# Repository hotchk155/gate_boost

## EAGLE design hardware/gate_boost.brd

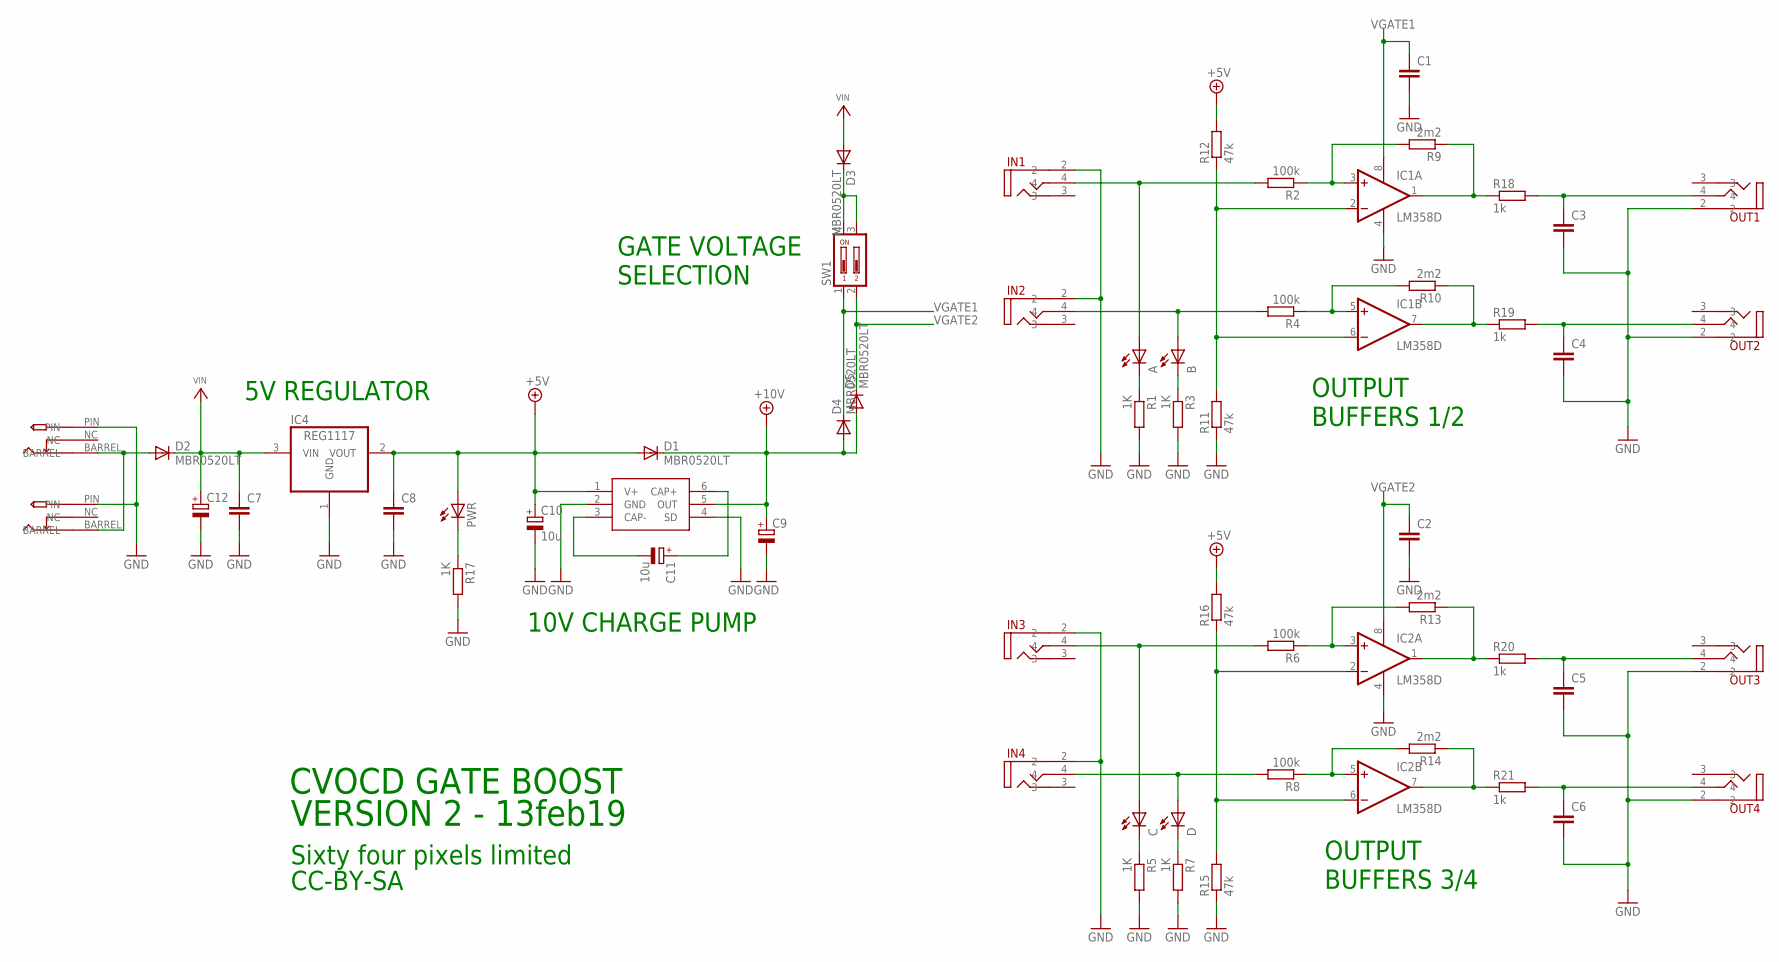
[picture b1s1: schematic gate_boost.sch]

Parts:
A: LED3MM
B: LED3MM
C: LED3MM
C1, C2, C3, C4, C5, C6, C7, C8: C-EUC0805; C0805
C9: CPOL-EUSMCA; SMC_A
C10, C11: 10u; SMC_A
C12: CPOL-EUE2-5; E2-5
D: LED3MM
D1, D2, D3, D4, D5: MBR0520LT; SOD123
IC1, IC2: LM358D; SO08
IC3: LM27675M5_CHARGEPUMP; SOT23-6
IC4: REG1117; SOT223
IN1, IN2, IN3, IN4: VERTICAL_3_5MM_SOCKET
OUT1, OUT2, OUT3, OUT4: VERTICAL_3_5MM_SOCKET
PWR: LED3MM
R1, R3, R5, R7, R17: 1K; R0805
R2, R4, R6, R8: 100k; R0805
R9, R10, R13, R14: 2m2; R0805
R11, R12, R15, R16: 47k; R0805
R18, R19, R20, R21: 1k; R0805
SW1: DIP02YL
U$1, U$2: PWR_SOCKET_2_1MM

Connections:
+5V: C8.1, C10.+, D1.A, IC3.1 (V+), IC4.2 (VOUT), PWR.A, R12.2, R16.2
+10V: C9.+, D1.C, D4.A, D5.A, IC3.5 (OUT)
GND: C1.2, C2.2, C3.2, C4.2, C5.2, C6.2, C7.2, C8.2, C9.-, C10.-, C12.-, IC1.4 (V-), IC2.4 (V-), IC3.2 (GND), IC3.4 (SD), IC4.1 (GND), IN1.2, IN2.2, IN3.2, IN4.2, OUT1.2, OUT2.2, OUT3.2, OUT4.2, R1.2, R3.2, R5.2, R7.2, R11.1, R15.1, R17.2, U$1.PIN, U$2.PIN
IN1: A.A, IN1.4, R2.2
IN2: B.A, IN2.4, R4.2
IN3: C.A, IN3.4, R6.2
IN4: D.A, IN4.4, R8.2
unnamed: IC1.2 (-IN), IC1.6 (-IN), R11.2, R12.1
unnamed: A.K (C), R1.1
unnamed: B.K (C), R3.1
unnamed: IC1.3 (+IN), R2.1, R9.2
unnamed: IC1.5 (+IN), R4.1, R10.2
unnamed: D3.C, SW1.3, SW1.4
unnamed: C5.1, OUT3.4, R20.2
unnamed: C6.1, OUT4.4, R21.2
unnamed: IC1.1 (OUT), R9.1, R18.1
unnamed: IC2.7 (OUT), R14.1, R21.1
unnamed: IC2.1 (OUT), R13.1, R20.1
unnamed: IC1.7 (OUT), R10.1, R19.1
unnamed: IC2.2 (-IN), IC2.6 (-IN), R15.2, R16.1
unnamed: C.K (C), R5.1
unnamed: D.K (C), R7.1
unnamed: IC2.3 (+IN), R6.1, R13.2
unnamed: IC2.5 (+IN), R8.1, R14.2
unnamed: C3.1, OUT1.4, R18.2
unnamed: C4.1, OUT2.4, R19.2
unnamed: D2.A, U$1.BARREL, U$2.BARREL
unnamed: PWR.K (C), R17.1
unnamed: C11.+, IC3.6 (CAP+)
unnamed: C11.-, IC3.3 (CAP-)
VGATE1: C1.1, D4.C, IC1.8 (V+), SW1.1
VGATE2: C2.1, D5.C, IC2.8 (V+), SW1.2
VIN: C7.1, C12.+, D2.C, D3.A, IC4.3 (VIN)

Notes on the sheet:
10V CHARGE PUMP
CVOCD GATE BOOST
VERSION 2 - 13feb19
Sixty four pixels limited
CC-BY-SA
5V REGULATOR
GATE VOLTAGE SELECTION
OUTPUT BUFFERS 1/2
OUTPUT BUFFERS 3/4

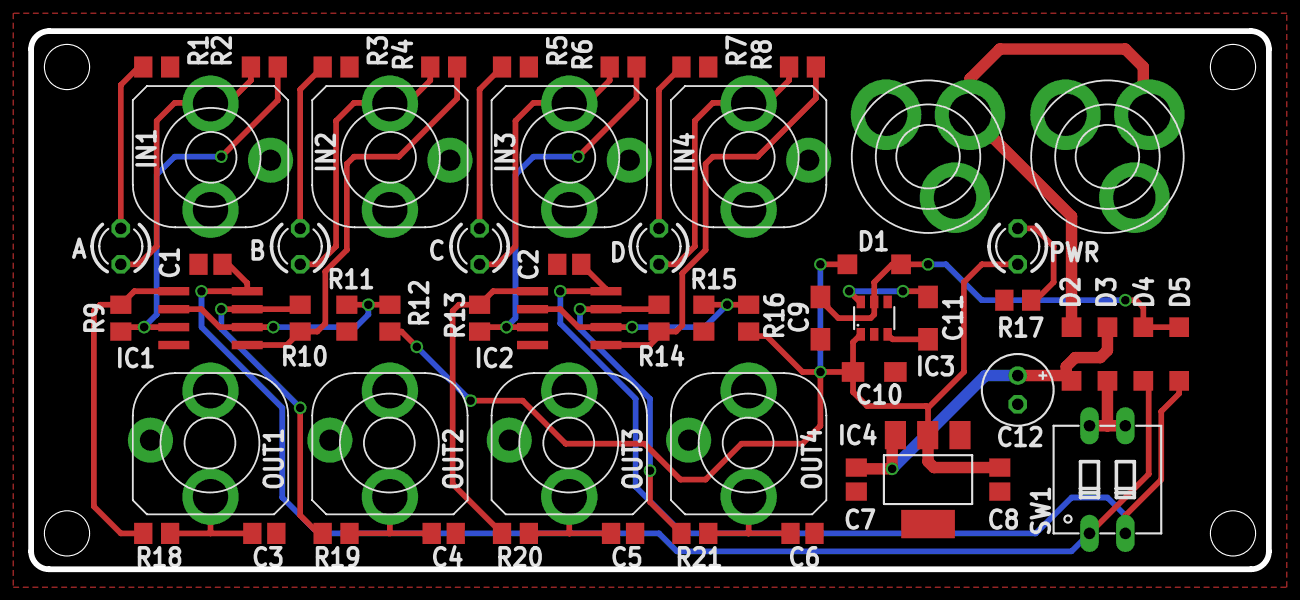
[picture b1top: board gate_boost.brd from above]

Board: 2 copper layers, 87.6 x 38.1 mm, 58 parts (0 on the bottom side), 33 nets.

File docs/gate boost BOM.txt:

R1, R3, R5, R7, R17, R18, R19, R20, R21   	1K resistor 0805
R2, R4, R6, R8   							100k resistor 0805
R9, R10, R13, R14   						2m2 resistor 0805
R11, R12, R15, R16  						47k resistor 0805

C1, C2, C7, C8 								100n Ceramic cap 0805
C3, C4, C5, C6 								10n Ceramic cap 0805
C9, C10, C11  								10u Tantalum "A" case
C12 										47uF/16V electrolytic

D1, D2, D3, D4, D5   						MBR0520LT schottky diode

IC1, IC2 									TSX7192IDT SOIC-8 dual op amp r/r 
IC3  										LM27675M5 charge pump SOT23-6                                                                                                
IC4  										REG1117 +5V regulator SOT223

A, B, C, D 									1.8mm Blue LED
PWR 										1.8mm Red LED

SW1 										Dual DIP switch 02YL

IN1, IN2, IN3, IN4, OUT1, OUT2, OUT3, OUT4  VERTICAL 3.5MM SOCKET
U$1, U$2  									PWR_SOCKET_2_1MM

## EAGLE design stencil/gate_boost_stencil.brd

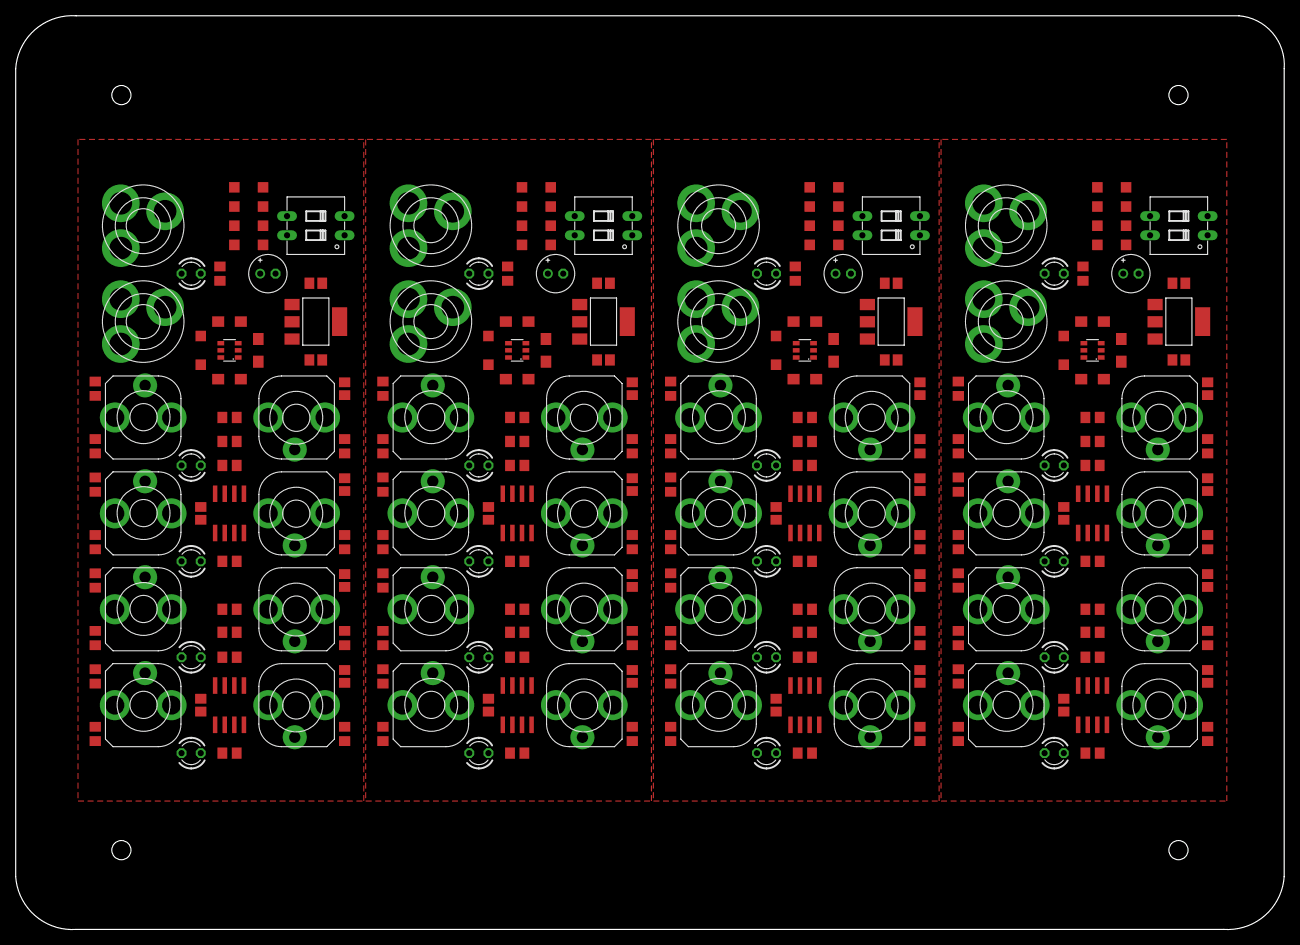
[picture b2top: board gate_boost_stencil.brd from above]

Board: 2 copper layers, 168.0 x 121.0 mm, 236 parts (0 on the bottom side), 132 nets, no tracks yet.

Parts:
A, A1, A2, A3: LED3MM
B, B1, B2, B3: LED3MM
C, C19, C32, C45: LED3MM
C1, C2, C3, C4, C5, C6, C7, C8, C13, C14, C18, C20, C21, C22, C24, C25, C26, C27, C31, C33, C34, C35, C37, C38, C39, C40, C44, C46, C47, C48, C50, C51: C0805
C9, C16, C29, C42: SMC_A
C10, C11, C15, C17, C28, C30, C41, C43: 10u; SMC_A
C12, C23, C36, C49: E2-5
D, D7, D13, D19: LED3MM
D1, D2, D3, D4, D5, D6, D8, D9, D10, D11, D12, D14, D15, D16, D17, D18, D20, D21, D22, D23: MBR0520LT; SOD123
E$4, E$5, E$6, E$7: STENCILPIN
IC1, IC2, IC6, IC7, IC10, IC11, IC14, IC15: LM358D; SO08
IC3, IC5, IC9, IC13: LM27675M5_CHARGEPUMP; SOT23-6
IC4, IC8, IC12, IC16: REG1117; SOT223
IN1, IN2, IN3, IN4, IN5, IN6, IN7, IN8, IN9, IN10, IN11, IN12, IN13, IN14, IN15, IN16: VERTICAL_3_5MM_SOCKET
OUT1, OUT2, OUT3, OUT4, OUT5, OUT6, OUT7, OUT8, OUT9, OUT10, OUT11, OUT12, OUT13, OUT14, OUT15, OUT16: VERTICAL_3_5MM_SOCKET
PWR, PWR1, PWR2, PWR3: LED3MM
R1, R3, R5, R7, R17, R22, R23, R32, R33, R42, R43, R44, R53, R54, R63, R64, R65, R74, R75, R84: 1K; R0805
R2, R4, R6, R8, R28, R29, R38, R39, R49, R50, R59, R60, R70, R71, R80, R81: 100k; R0805
R9, R10, R13, R14, R30, R31, R40, R41, R51, R52, R61, R62, R72, R73, R82, R83: 2m2; R0805
R11, R12, R15, R16, R26, R27, R36, R37, R47, R48, R57, R58, R68, R69, R78, R79: 47k; R0805
R18, R19, R20, R21, R24, R25, R34, R35, R45, R46, R55, R56, R66, R67, R76, R77: 1k; R0805
SW1, SW2, SW3, SW4: DIP02YL
U$1, U$2, U$3, U$4, U$5, U$6, U$7, U$8: PWR_SOCKET_2_1MM

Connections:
+5V: C8.1, C10.+, D1.A, IC3.1, IC4.2, PWR.A, R12.2, R16.2
+5V1: C17.+, C25.1, D6.A, IC5.1, IC8.2, PWR1.A, R27.2, R37.2
+5V2: C30.+, C38.1, D12.A, IC9.1, IC12.2, PWR2.A, R48.2, R58.2
+5V3: C43.+, C51.1, D18.A, IC13.1, IC16.2, PWR3.A, R69.2, R79.2
+10V: C9.+, D1.C, D4.A, D5.A, IC3.5
+10V1: C16.+, D6.C, D9.A, D10.A, IC5.5
+10V2: C29.+, D12.C, D15.A, D16.A, IC9.5
+10V3: C42.+, D18.C, D21.A, D22.A, IC13.5
GND: C1.2, C2.2, C3.2, C4.2, C5.2, C6.2, C7.2, C8.2, C9.-, C10.-, C12.-, IC1.4, IC2.4, IC3.2, IC3.4, IC4.1, IN1.2, IN2.2, IN3.2, IN4.2, OUT1.2, OUT2.2, OUT3.2, OUT4.2, R1.2, R3.2, R5.2, R7.2, R11.1, R15.1, R17.2, U$1.PIN, U$2.PIN
GND1: C13.2, C14.2, C16.-, C17.-, C18.2, C20.2, C21.2, C22.2, C23.-, C24.2, C25.2, IC5.2, IC5.4, IC6.4, IC7.4, IC8.1, IN5.2, IN6.2, IN7.2, IN8.2, OUT5.2, OUT6.2, OUT7.2, OUT8.2, R22.2, R23.2, R26.1, R32.2, R33.2, R36.1, R42.2, U$3.PIN, U$4.PIN
GND2: C26.2, C27.2, C29.-, C30.-, C31.2, C33.2, C34.2, C35.2, C36.-, C37.2, C38.2, IC9.2, IC9.4, IC10.4, IC11.4, IC12.1, IN9.2, IN10.2, IN11.2, IN12.2, OUT9.2, OUT10.2, OUT11.2, OUT12.2, R43.2, R44.2, R47.1, R53.2, R54.2, R57.1, R63.2, U$5.PIN, U$6.PIN
GND3: C39.2, C40.2, C42.-, C43.-, C44.2, C46.2, C47.2, C48.2, C49.-, C50.2, C51.2, IC13.2, IC13.4, IC14.4, IC15.4, IC16.1, IN13.2, IN14.2, IN15.2, IN16.2, OUT13.2, OUT14.2, OUT15.2, OUT16.2, R64.2, R65.2, R68.1, R74.2, R75.2, R78.1, R84.2, U$7.PIN, U$8.PIN
IN1: A.A, IN1.4, R2.2
IN2: B.A, IN2.4, R4.2
IN3: C.A, IN3.4, R6.2
IN4: D.A, IN4.4, R8.2
IN5: C19.A, IN7.4, R38.2
IN6: D7.A, IN8.4, R39.2
IN7: A1.A, IN5.4, R28.2
IN8: B1.A, IN6.4, R29.2
IN9: C32.A, IN11.4, R59.2
IN10: D13.A, IN12.4, R60.2
IN11: A2.A, IN9.4, R49.2
IN12: B2.A, IN10.4, R50.2
IN13: C45.A, IN15.4, R80.2
IN14: D19.A, IN16.4, R81.2
IN15: A3.A, IN13.4, R70.2
IN16: B3.A, IN14.4, R71.2
unnamed: IC1.2, IC1.6, R11.2, R12.1
unnamed: A.K, R1.1
unnamed: B.K, R3.1
unnamed: IC1.3, R2.1, R9.2
unnamed: IC1.5, R4.1, R10.2
unnamed: D3.C, SW1.3, SW1.4
unnamed: C5.1, OUT3.4, R20.2
unnamed: C6.1, OUT4.4, R21.2
unnamed: IC1.1, R9.1, R18.1
unnamed: IC2.7, R14.1, R21.1
unnamed: IC2.1, R13.1, R20.1
unnamed: IC1.7, R10.1, R19.1
unnamed: IC2.2, IC2.6, R15.2, R16.1
unnamed: C.K, R5.1
unnamed: D.K, R7.1
unnamed: IC2.3, R6.1, R13.2
unnamed: IC2.5, R8.1, R14.2
unnamed: C13.1, OUT5.4, R24.2
unnamed: C3.1, OUT1.4, R18.2
unnamed: C4.1, OUT2.4, R19.2
unnamed: D2.A, U$1.BARREL, U$2.BARREL
unnamed: C14.1, OUT6.4, R25.2
unnamed: PWR.K, R17.1
unnamed: IC6.7, R25.1, R30.1
unnamed: IC6.1, R24.1, R31.1
unnamed: C15.+, IC5.6
unnamed: C15.-, IC5.3
unnamed: IC6.2, IC6.6, R26.2, R27.1
unnamed: A1.K, R23.1
unnamed: B1.K, R22.1
unnamed: IC6.3, R28.1, R31.2
unnamed: IC6.5, R29.1, R30.2
unnamed: C20.1, OUT7.4, R34.2
unnamed: C21.1, OUT8.4, R35.2
unnamed: IC7.7, R35.1, R40.1
unnamed: IC7.1, R34.1, R41.1
unnamed: IC7.2, IC7.6, R36.2, R37.1
unnamed: C11.+, IC3.6
unnamed: C11.-, IC3.3
unnamed: C19.K, R33.1
unnamed: D7.K, R32.1
unnamed: IC7.3, R38.1, R41.2
unnamed: IC7.5, R39.1, R40.2
unnamed: D8.A, U$3.BARREL, U$4.BARREL
unnamed: PWR1.K, R42.1
unnamed: D11.C, SW2.3, SW2.4
unnamed: C26.1, OUT9.4, R45.2
unnamed: C27.1, OUT10.4, R46.2
unnamed: IC10.7, R46.1, R51.1
unnamed: IC10.1, R45.1, R52.1
unnamed: C28.+, IC9.6
unnamed: C28.-, IC9.3
unnamed: IC10.2, IC10.6, R47.2, R48.1
unnamed: A2.K, R44.1
unnamed: B2.K, R43.1
unnamed: IC10.3, R49.1, R52.2
unnamed: IC10.5, R50.1, R51.2
unnamed: C33.1, OUT11.4, R55.2
unnamed: C34.1, OUT12.4, R56.2
unnamed: IC11.7, R56.1, R61.1
unnamed: IC11.1, R55.1, R62.1
unnamed: IC11.2, IC11.6, R57.2, R58.1
unnamed: C32.K, R54.1
unnamed: D13.K, R53.1
unnamed: IC11.3, R59.1, R62.2
unnamed: IC11.5, R60.1, R61.2
unnamed: D14.A, U$5.BARREL, U$6.BARREL
unnamed: PWR2.K, R63.1
unnamed: D17.C, SW3.3, SW3.4
unnamed: C39.1, OUT13.4, R66.2
unnamed: C40.1, OUT14.4, R67.2
unnamed: IC14.7, R67.1, R72.1
unnamed: IC14.1, R66.1, R73.1
unnamed: C41.+, IC13.6
unnamed: C41.-, IC13.3
unnamed: IC14.2, IC14.6, R68.2, R69.1
unnamed: A3.K, R65.1
unnamed: B3.K, R64.1
unnamed: IC14.3, R70.1, R73.2
unnamed: IC14.5, R71.1, R72.2
unnamed: C46.1, OUT15.4, R76.2
unnamed: C47.1, OUT16.4, R77.2
unnamed: IC15.7, R77.1, R82.1
unnamed: IC15.1, R76.1, R83.1
unnamed: IC15.2, IC15.6, R78.2, R79.1
unnamed: C45.K, R75.1
unnamed: D19.K, R74.1
unnamed: IC15.3, R80.1, R83.2
unnamed: IC15.5, R81.1, R82.2
unnamed: D20.A, U$7.BARREL, U$8.BARREL
unnamed: PWR3.K, R84.1
unnamed: D23.C, SW4.3, SW4.4
VGATE1: C1.1, D4.C, IC1.8, SW1.1
VGATE2: C2.1, D5.C, IC2.8, SW1.2
VGATE3: C22.1, D10.C, IC7.8, SW2.2
VGATE4: C18.1, D9.C, IC6.8, SW2.1
VGATE5: C35.1, D16.C, IC11.8, SW3.2
VGATE6: C31.1, D15.C, IC10.8, SW3.1
VGATE7: C48.1, D22.C, IC15.8, SW4.2
VGATE8: C44.1, D21.C, IC14.8, SW4.1
VIN: C7.1, C12.+, D2.C, D3.A, IC4.3
VIN1: C23.+, C24.1, D8.C, D11.A, IC8.3
VIN2: C36.+, C37.1, D14.C, D17.A, IC12.3
VIN3: C49.+, C50.1, D20.C, D23.A, IC16.3

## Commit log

2017-07-12 :octocat: Added .gitattributes & .gitignore files
2017-07-12 initial
2019-01-10 prior change to charge pump
2019-01-10 charge pump
2019-01-10 getting there
2019-01-28 component values
2019-02-27 V2 additional schottky on VIN
2019-02-27 tidy tidy
2019-02-27 Update gate_boost_panel.brd
    das
2019-02-27 asdds
2019-03-27 docs
2022-01-11 asdas
2022-01-12 V1 of PCB for front panel
2022-03-07 red LEDs
